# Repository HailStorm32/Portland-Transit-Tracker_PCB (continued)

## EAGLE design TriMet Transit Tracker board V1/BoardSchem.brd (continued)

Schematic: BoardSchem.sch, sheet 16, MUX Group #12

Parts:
IC27, IC28: 74ALVC04PW,118; SOP65P640X110-14N
R60, R61, R62, R63, R64, R65, R66, R67: 50; R0805
U13: 74LCX138MX; SOIC127P600X175-16N
Y1G12, Y2G12, Y3G12, Y4G12, Y5G12, Y6G12, Y7G12, Y8G12: LTST-C170TBKT; LEDC2012X120N

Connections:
+3V3: IC27.14 (VCC), IC28.14 (VCC), U13.16 (VCC); also elsewhere on the board
GND: IC27.7 (GND), IC28.7 (GND), R60.1, R61.1, R62.1, R63.1, R64.1, R65.1, R66.1, R67.1, U13.4 (~E1), U13.5 (~E2), U13.8 (GND); also elsewhere on the board
MUX_GROUP_12: U13.6 (E3); also elsewhere on the board
unnamed: IC27.1 (1A), U13.15 (~O0)
unnamed: IC27.2 (1Y), Y1G12.2 (A)
unnamed: IC27.3 (2A), U13.14 (~O1)
unnamed: IC27.4 (2Y), Y2G12.2 (A)
unnamed: IC27.5 (3A), U13.13 (~O2)
unnamed: IC27.6 (3Y), Y3G12.2 (A)
unnamed: IC27.13 (6A), U13.12 (~O3)
unnamed: IC27.12 (6Y), Y4G12.2 (A)
unnamed: IC27.11 (5A), U13.11 (~O4)
unnamed: IC27.10 (5Y), Y5G12.2 (A)
unnamed: IC27.9 (4A), U13.10 (~O5)
unnamed: IC27.8 (4Y), Y6G12.2 (A)
unnamed: IC28.1 (1A), U13.9 (~O6)
unnamed: IC28.2 (1Y), Y7G12.2 (A)
unnamed: IC28.3 (2A), U13.7 (~O7)
unnamed: IC28.4 (2Y), Y8G12.2 (A)
unnamed: R60.2, Y1G12.1 (K)
unnamed: R61.2, Y2G12.1 (K)
unnamed: R62.2, Y3G12.1 (K)
unnamed: R63.2, Y4G12.1 (K)
unnamed: R64.2, Y5G12.1 (K)
unnamed: R65.2, Y6G12.1 (K)
unnamed: R66.2, Y7G12.1 (K)
unnamed: R67.2, Y8G12.1 (K)
Q0: U13.1 (A0); also elsewhere on the board
Q1: U13.2 (A1); also elsewhere on the board
Q2: U13.3 (A2); also elsewhere on the board

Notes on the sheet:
Blue dont need resistors
MUX Group #12

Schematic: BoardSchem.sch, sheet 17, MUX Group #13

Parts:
B1G13, B2G13, B3G13, B4G13, B5G13, B6G13, B7G13, B8G13: LTST-C170TBKT; LEDC2012X120N
IC29, IC30: 74ALVC04PW,118; SOP65P640X110-14N
U14: 74LCX138MX; SOIC127P600X175-16N

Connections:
+3V3: IC29.14 (VCC), IC30.14 (VCC), U14.16 (VCC); also elsewhere on the board
GND: B1G13.1 (K), B2G13.1 (K), B3G13.1 (K), B4G13.1 (K), B5G13.1 (K), B6G13.1 (K), B7G13.1 (K), B8G13.1 (K), IC29.7 (GND), IC30.7 (GND), U14.4 (~E1), U14.5 (~E2), U14.8 (GND); also elsewhere on the board
MUX_GROUP_13: U14.6 (E3); also elsewhere on the board
unnamed: IC29.1 (1A), U14.15 (~O0)
unnamed: B1G13.2 (A), IC29.2 (1Y)
unnamed: IC29.3 (2A), U14.14 (~O1)
unnamed: B2G13.2 (A), IC29.4 (2Y)
unnamed: IC29.5 (3A), U14.13 (~O2)
unnamed: B3G13.2 (A), IC29.6 (3Y)
unnamed: IC29.13 (6A), U14.12 (~O3)
unnamed: B4G13.2 (A), IC29.12 (6Y)
unnamed: IC29.11 (5A), U14.11 (~O4)
unnamed: B5G13.2 (A), IC29.10 (5Y)
unnamed: IC29.9 (4A), U14.10 (~O5)
unnamed: B6G13.2 (A), IC29.8 (4Y)
unnamed: IC30.1 (1A), U14.9 (~O6)
unnamed: B7G13.2 (A), IC30.2 (1Y)
unnamed: IC30.3 (2A), U14.7 (~O7)
unnamed: B8G13.2 (A), IC30.4 (2Y)
Q0: U14.1 (A0); also elsewhere on the board
Q1: U14.2 (A1); also elsewhere on the board
Q2: U14.3 (A2); also elsewhere on the board

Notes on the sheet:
Blue dont need resistors
MUX Group #13

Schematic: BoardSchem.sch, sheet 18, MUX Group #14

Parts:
G1G14, G2G14, G3G14, G4G14, G5G14, G6G14, G7G14, G8G14: LTST-C170TBKT; LEDC2012X120N
IC31, IC32: 74ALVC04PW,118; SOP65P640X110-14N
R68, R69, R70, R71, R72, R73, R74, R75: 50; R0805
U15: 74LCX138MX; SOIC127P600X175-16N

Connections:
+3V3: IC31.14 (VCC), IC32.14 (VCC), U15.16 (VCC); also elsewhere on the board
GND: IC31.7 (GND), IC32.7 (GND), R68.1, R69.1, R70.1, R71.1, R72.1, R73.1, R74.1, R75.1, U15.4 (~E1), U15.5 (~E2), U15.8 (GND); also elsewhere on the board
MUX_GROUP_14: U15.6 (E3); also elsewhere on the board
unnamed: IC31.1 (1A), U15.15 (~O0)
unnamed: G1G14.2 (A), IC31.2 (1Y)
unnamed: IC31.3 (2A), U15.14 (~O1)
unnamed: G2G14.2 (A), IC31.4 (2Y)
unnamed: IC31.5 (3A), U15.13 (~O2)
unnamed: G3G14.2 (A), IC31.6 (3Y)
unnamed: IC31.13 (6A), U15.12 (~O3)
unnamed: G4G14.2 (A), IC31.12 (6Y)
unnamed: IC31.11 (5A), U15.11 (~O4)
unnamed: G5G14.2 (A), IC31.10 (5Y)
unnamed: IC31.9 (4A), U15.10 (~O5)
unnamed: G6G14.2 (A), IC31.8 (4Y)
unnamed: IC32.1 (1A), U15.9 (~O6)
unnamed: G7G14.2 (A), IC32.2 (1Y)
unnamed: IC32.3 (2A), U15.7 (~O7)
unnamed: G8G14.2 (A), IC32.4 (2Y)
unnamed: G1G14.1 (K), R68.2
unnamed: G2G14.1 (K), R69.2
unnamed: G3G14.1 (K), R70.2
unnamed: G4G14.1 (K), R71.2
unnamed: G5G14.1 (K), R72.2
unnamed: G6G14.1 (K), R73.2
unnamed: G7G14.1 (K), R74.2
unnamed: G8G14.1 (K), R75.2
Q0: U15.1 (A0); also elsewhere on the board
Q1: U15.2 (A1); also elsewhere on the board
Q2: U15.3 (A2); also elsewhere on the board

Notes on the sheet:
Blue dont need resistors
MUX Group #14

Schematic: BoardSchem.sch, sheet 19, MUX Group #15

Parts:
IC33, IC34: 74ALVC04PW,118; SOP65P640X110-14N
R1G15, R2G15, R3G15, R4G15, R5G15, R6G15, R7G15, R8G15: LTST-C170TBKT; LEDC2012X120N
R76, R77, R78, R79, R80, R81, R82, R83: 50; R0805
U16: 74LCX138MX; SOIC127P600X175-16N

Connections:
+3V3: IC33.14 (VCC), IC34.14 (VCC), U16.16 (VCC); also elsewhere on the board
GND: IC33.7 (GND), IC34.7 (GND), R76.1, R77.1, R78.1, R79.1, R80.1, R81.1, R82.1, R83.1, U16.4 (~E1), U16.5 (~E2), U16.8 (GND); also elsewhere on the board
MUX_GROUP_15: U16.6 (E3); also elsewhere on the board
unnamed: IC33.1 (1A), U16.15 (~O0)
unnamed: IC33.2 (1Y), R1G15.2 (A)
unnamed: IC33.3 (2A), U16.14 (~O1)
unnamed: IC33.4 (2Y), R2G15.2 (A)
unnamed: IC33.5 (3A), U16.13 (~O2)
unnamed: IC33.6 (3Y), R3G15.2 (A)
unnamed: IC33.13 (6A), U16.12 (~O3)
unnamed: IC33.12 (6Y), R4G15.2 (A)
unnamed: IC33.11 (5A), U16.11 (~O4)
unnamed: IC33.10 (5Y), R5G15.2 (A)
unnamed: IC33.9 (4A), U16.10 (~O5)
unnamed: IC33.8 (4Y), R6G15.2 (A)
unnamed: IC34.1 (1A), U16.9 (~O6)
unnamed: IC34.2 (1Y), R7G15.2 (A)
unnamed: IC34.3 (2A), U16.7 (~O7)
unnamed: IC34.4 (2Y), R8G15.2 (A)
unnamed: R1G15.1 (K), R76.2
unnamed: R2G15.1 (K), R77.2
unnamed: R3G15.1 (K), R78.2
unnamed: R4G15.1 (K), R79.2
unnamed: R5G15.1 (K), R80.2
unnamed: R6G15.1 (K), R81.2
unnamed: R7G15.1 (K), R82.2
unnamed: R8G15.1 (K), R83.2
Q0: U16.1 (A0); also elsewhere on the board
Q1: U16.2 (A1); also elsewhere on the board
Q2: U16.3 (A2); also elsewhere on the board

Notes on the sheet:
Blue dont need resistors
MUX Group #15

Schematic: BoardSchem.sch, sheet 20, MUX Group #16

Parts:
B1G16, B2G16, B3G16, B4G16, B5G16, B6G16, B7G16, B8G16: LTST-C170TBKT; LEDC2012X120N
IC35, IC36: 74ALVC04PW,118; SOP65P640X110-14N
U17: 74LCX138MX; SOIC127P600X175-16N

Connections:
+3V3: IC35.14 (VCC), IC36.14 (VCC), U17.16 (VCC); also elsewhere on the board
GND: B1G16.1 (K), B2G16.1 (K), B3G16.1 (K), B4G16.1 (K), B5G16.1 (K), B6G16.1 (K), B7G16.1 (K), B8G16.1 (K), IC35.7 (GND), IC36.7 (GND), U17.4 (~E1), U17.5 (~E2), U17.8 (GND); also elsewhere on the board
MUX_GROUP_16: U17.6 (E3); also elsewhere on the board
unnamed: IC35.1 (1A), U17.15 (~O0)
unnamed: B1G16.2 (A), IC35.2 (1Y)
unnamed: IC35.3 (2A), U17.14 (~O1)
unnamed: B2G16.2 (A), IC35.4 (2Y)
unnamed: IC35.5 (3A), U17.13 (~O2)
unnamed: B3G16.2 (A), IC35.6 (3Y)
unnamed: IC35.13 (6A), U17.12 (~O3)
unnamed: B4G16.2 (A), IC35.12 (6Y)
unnamed: IC35.11 (5A), U17.11 (~O4)
unnamed: B5G16.2 (A), IC35.10 (5Y)
unnamed: IC35.9 (4A), U17.10 (~O5)
unnamed: B6G16.2 (A), IC35.8 (4Y)
unnamed: IC36.1 (1A), U17.9 (~O6)
unnamed: B7G16.2 (A), IC36.2 (1Y)
unnamed: IC36.3 (2A), U17.7 (~O7)
unnamed: B8G16.2 (A), IC36.4 (2Y)
Q0: U17.1 (A0); also elsewhere on the board
Q1: U17.2 (A1); also elsewhere on the board
Q2: U17.3 (A2); also elsewhere on the board

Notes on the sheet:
Blue dont need resistors
MUX Group #16

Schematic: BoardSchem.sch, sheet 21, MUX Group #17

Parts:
B3G17, B4G17, B5G17, B6G17, B7G17, B8G17: LTST-C170TBKT; LEDC2012X120N
IC37, IC38: 74ALVC04PW,118; SOP65P640X110-14N
R1G17, R2G17: LTST-C170TBKT; LEDC2012X120N
R84, R85: 50; R0805
U18: 74LCX138MX; SOIC127P600X175-16N

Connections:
+3V3: IC37.14 (VCC), IC38.14 (VCC), U18.16 (VCC); also elsewhere on the board
GND: B3G17.1 (K), B4G17.1 (K), B5G17.1 (K), B6G17.1 (K), B7G17.1 (K), B8G17.1 (K), IC37.7 (GND), IC38.7 (GND), R84.1, R85.1, U18.4 (~E1), U18.5 (~E2), U18.8 (GND); also elsewhere on the board
MUX_GROUP_17: U18.6 (E3); also elsewhere on the board
unnamed: IC37.1 (1A), U18.15 (~O0)
unnamed: IC37.2 (1Y), R1G17.2 (A)
unnamed: IC37.3 (2A), U18.14 (~O1)
unnamed: IC37.4 (2Y), R2G17.2 (A)
unnamed: IC37.5 (3A), U18.13 (~O2)
unnamed: B3G17.2 (A), IC37.6 (3Y)
unnamed: IC37.13 (6A), U18.12 (~O3)
unnamed: B4G17.2 (A), IC37.12 (6Y)
unnamed: IC37.11 (5A), U18.11 (~O4)
unnamed: B5G17.2 (A), IC37.10 (5Y)
unnamed: IC37.9 (4A), U18.10 (~O5)
unnamed: B6G17.2 (A), IC37.8 (4Y)
unnamed: IC38.1 (1A), U18.9 (~O6)
unnamed: B7G17.2 (A), IC38.2 (1Y)
unnamed: IC38.3 (2A), U18.7 (~O7)
unnamed: B8G17.2 (A), IC38.4 (2Y)
unnamed: R1G17.1 (K), R84.2
unnamed: R2G17.1 (K), R85.2
Q0: U18.1 (A0); also elsewhere on the board
Q1: U18.2 (A1); also elsewhere on the board
Q2: U18.3 (A2); also elsewhere on the board

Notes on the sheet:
Blue dont need resistors
MUX Group #17

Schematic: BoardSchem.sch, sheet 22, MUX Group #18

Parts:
G1G18, G2G18, G3G18, G4G18, G5G18, G6G18, G7G18, G8G18: LTST-C170TBKT; LEDC2012X120N
IC39, IC40: 74ALVC04PW,118; SOP65P640X110-14N
R86, R87, R88, R89, R90, R91, R92, R93: 50; R0805
U19: 74LCX138MX; SOIC127P600X175-16N

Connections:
+3V3: IC39.14 (VCC), IC40.14 (VCC), U19.16 (VCC); also elsewhere on the board
GND: IC39.7 (GND), IC40.7 (GND), R86.1, R87.1, R88.1, R89.1, R90.1, R91.1, R92.1, R93.1, U19.4 (~E1), U19.5 (~E2), U19.8 (GND); also elsewhere on the board
MUX_GROUP_18: U19.6 (E3); also elsewhere on the board
unnamed: IC39.1 (1A), U19.15 (~O0)
unnamed: G1G18.2 (A), IC39.2 (1Y)
unnamed: IC39.3 (2A), U19.14 (~O1)
unnamed: G2G18.2 (A), IC39.4 (2Y)
unnamed: IC39.5 (3A), U19.13 (~O2)
unnamed: G3G18.2 (A), IC39.6 (3Y)
unnamed: IC39.13 (6A), U19.12 (~O3)
unnamed: G4G18.2 (A), IC39.12 (6Y)
unnamed: IC39.11 (5A), U19.11 (~O4)
unnamed: G5G18.2 (A), IC39.10 (5Y)
unnamed: IC39.9 (4A), U19.10 (~O5)
unnamed: G6G18.2 (A), IC39.8 (4Y)
unnamed: IC40.1 (1A), U19.9 (~O6)
unnamed: G7G18.2 (A), IC40.2 (1Y)
unnamed: IC40.3 (2A), U19.7 (~O7)
unnamed: G8G18.2 (A), IC40.4 (2Y)
unnamed: G1G18.1 (K), R86.2
unnamed: G2G18.1 (K), R87.2
unnamed: G3G18.1 (K), R88.2
unnamed: G4G18.1 (K), R89.2
unnamed: G5G18.1 (K), R90.2
unnamed: G6G18.1 (K), R91.2
unnamed: G7G18.1 (K), R92.2
unnamed: G8G18.1 (K), R93.2
Q0: U19.1 (A0); also elsewhere on the board
Q1: U19.2 (A1); also elsewhere on the board
Q2: U19.3 (A2); also elsewhere on the board

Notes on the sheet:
Blue dont need resistors
MUX Group #18

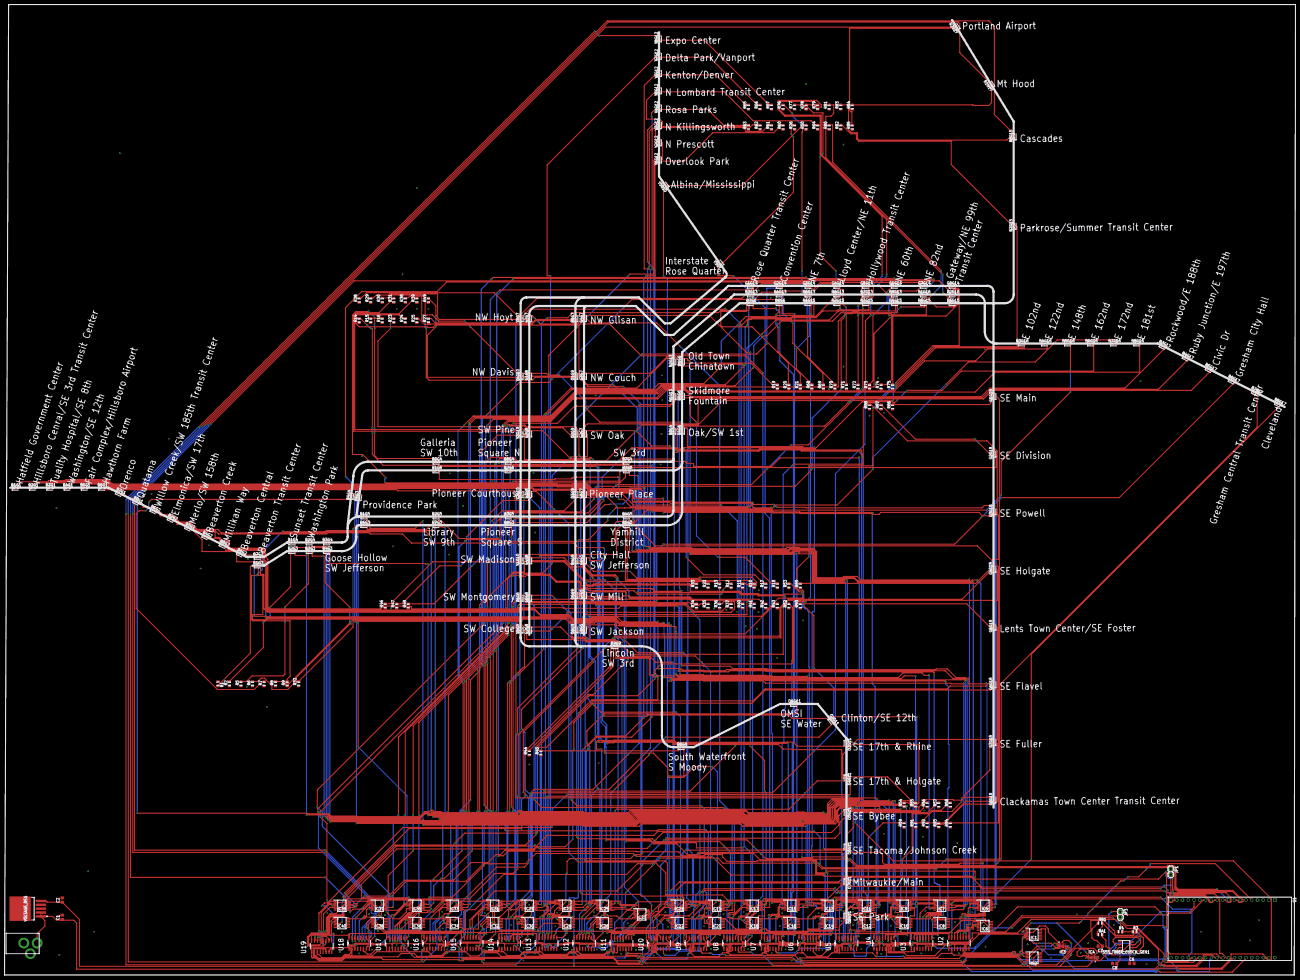
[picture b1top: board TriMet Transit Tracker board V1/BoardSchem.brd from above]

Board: 2 copper layers, 568.6 x 427.5 mm, 303 parts (0 on the bottom side), 412 nets.

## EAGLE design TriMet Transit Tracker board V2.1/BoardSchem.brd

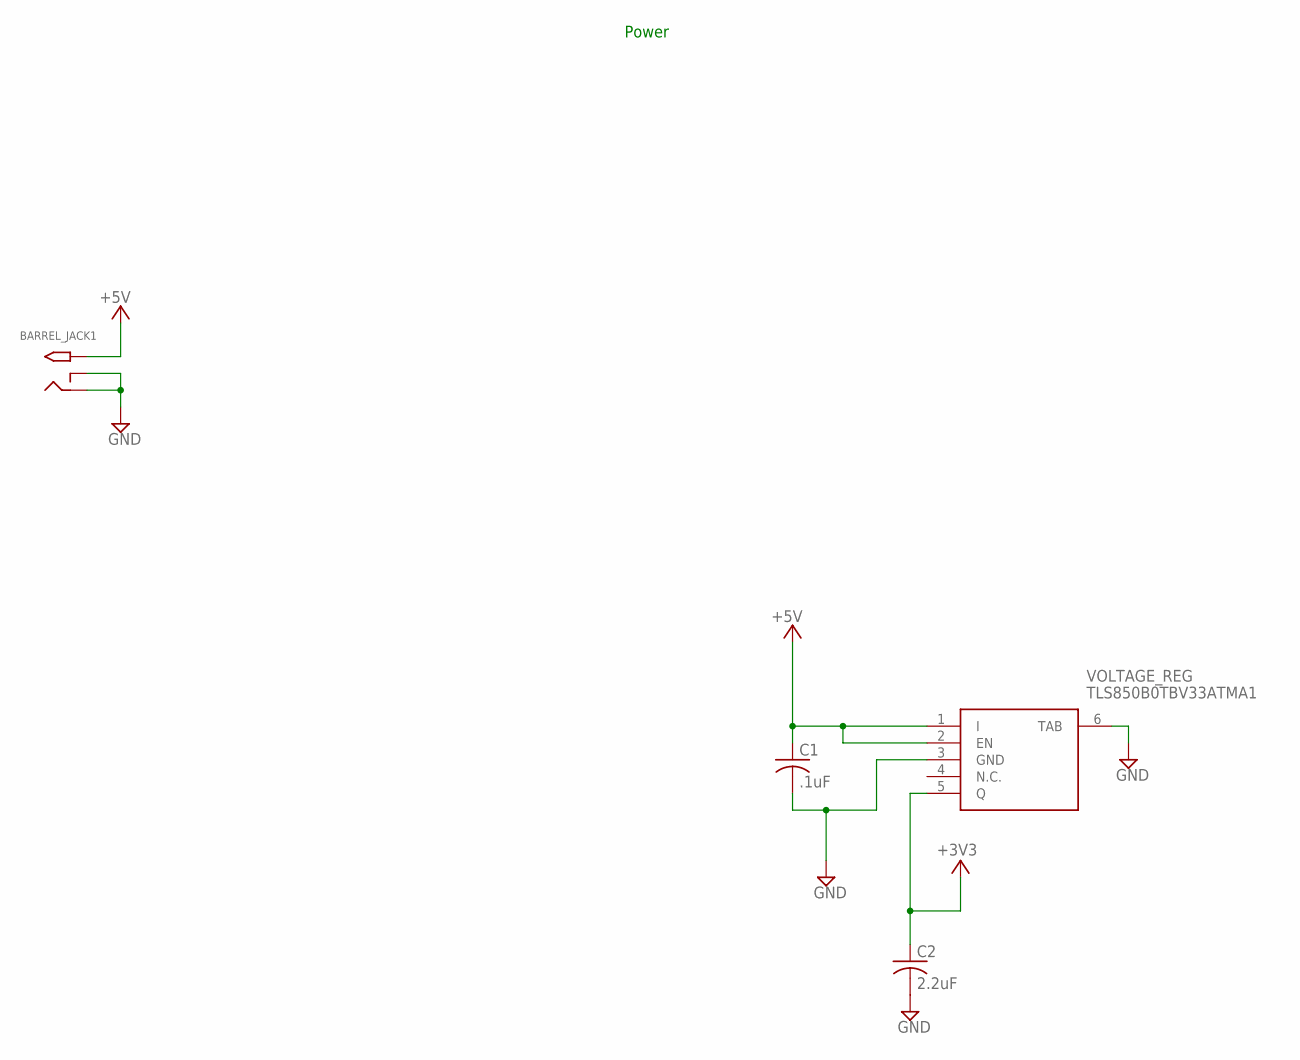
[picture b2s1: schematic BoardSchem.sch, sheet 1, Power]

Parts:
BARREL_JACK1: 2.1MMJACKTHM; PJ-102A
C1: .1uF; C0805
C2: 2.2uF; C0805
VOLTAGE_REG: TLS850B0TBV33ATMA1

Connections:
+3V3: C2.1, VOLTAGE_REG.5 (Q); also elsewhere on the board
+5V: BARREL_JACK1.TIP, C1.1, VOLTAGE_REG.1 (I), VOLTAGE_REG.2 (EN); also elsewhere on the board
GND: BARREL_JACK1.RING, BARREL_JACK1.RING_SW, C1.2, C2.2, VOLTAGE_REG.3 (GND), VOLTAGE_REG.6 (TAB); also elsewhere on the board

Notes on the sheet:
Power

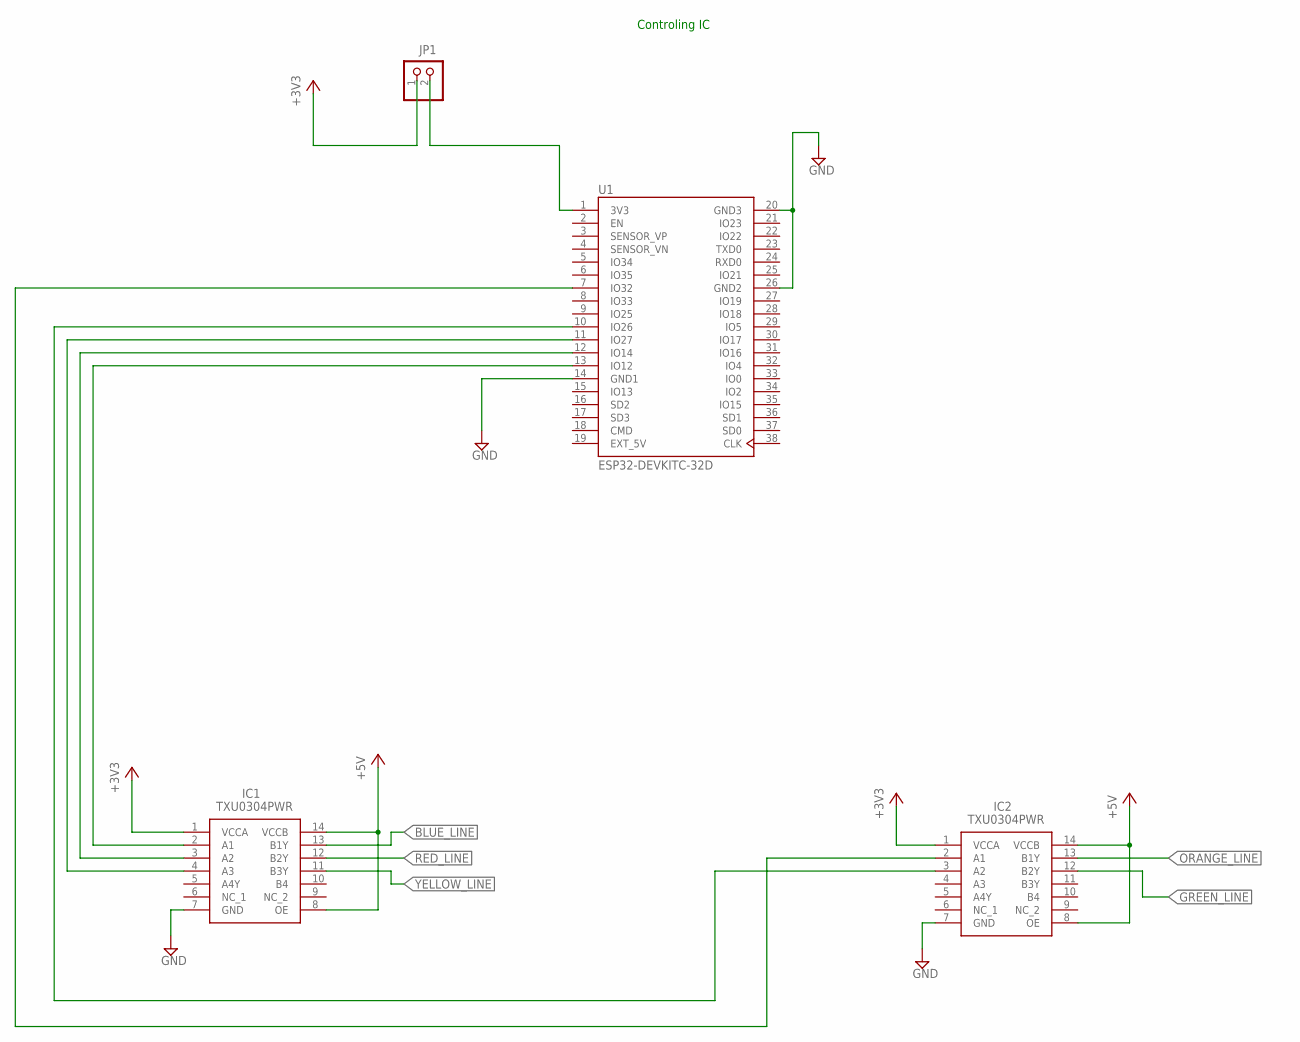
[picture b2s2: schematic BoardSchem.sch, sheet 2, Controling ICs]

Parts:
IC1, IC2: TXU0304PWR; SOP65P640X120-14N
JP1: PINHD-1X2; 1X02
U1: ESP32-DEVKITC-32D; MODULE_ESP32-DEVKITC-32D

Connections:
+3V3: IC1.1 (VCCA), IC2.1 (VCCA), JP1.1; also elsewhere on the board
+5V: IC1.8 (OE), IC1.14 (VCCB), IC2.8 (OE), IC2.14 (VCCB); also elsewhere on the board
BLUE_LINE: IC1.13 (B1Y); also elsewhere on the board
EXT_5V: U1.19 (EXT_5V)
GND: IC1.7 (GND), IC2.7 (GND), U1.14 (GND1), U1.20 (GND3), U1.26 (GND2); also elsewhere on the board
GREEN_LINE: IC2.12 (B2Y); also elsewhere on the board
unnamed: JP1.2, U1.1 (3V3)
unnamed: IC1.2 (A1), U1.13 (IO12)
unnamed: IC1.3 (A2), U1.12 (IO14)
unnamed: IC1.4 (A3), U1.11 (IO27)
unnamed: IC2.3 (A2), U1.10 (IO26)
unnamed: IC2.2 (A1), U1.7 (IO32)
ORANGE_LINE: IC2.13 (B1Y); also elsewhere on the board
RED_LINE: IC1.12 (B2Y); also elsewhere on the board
YELLOW_LINE: IC1.11 (B3Y); also elsewhere on the board

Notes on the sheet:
Controling IC

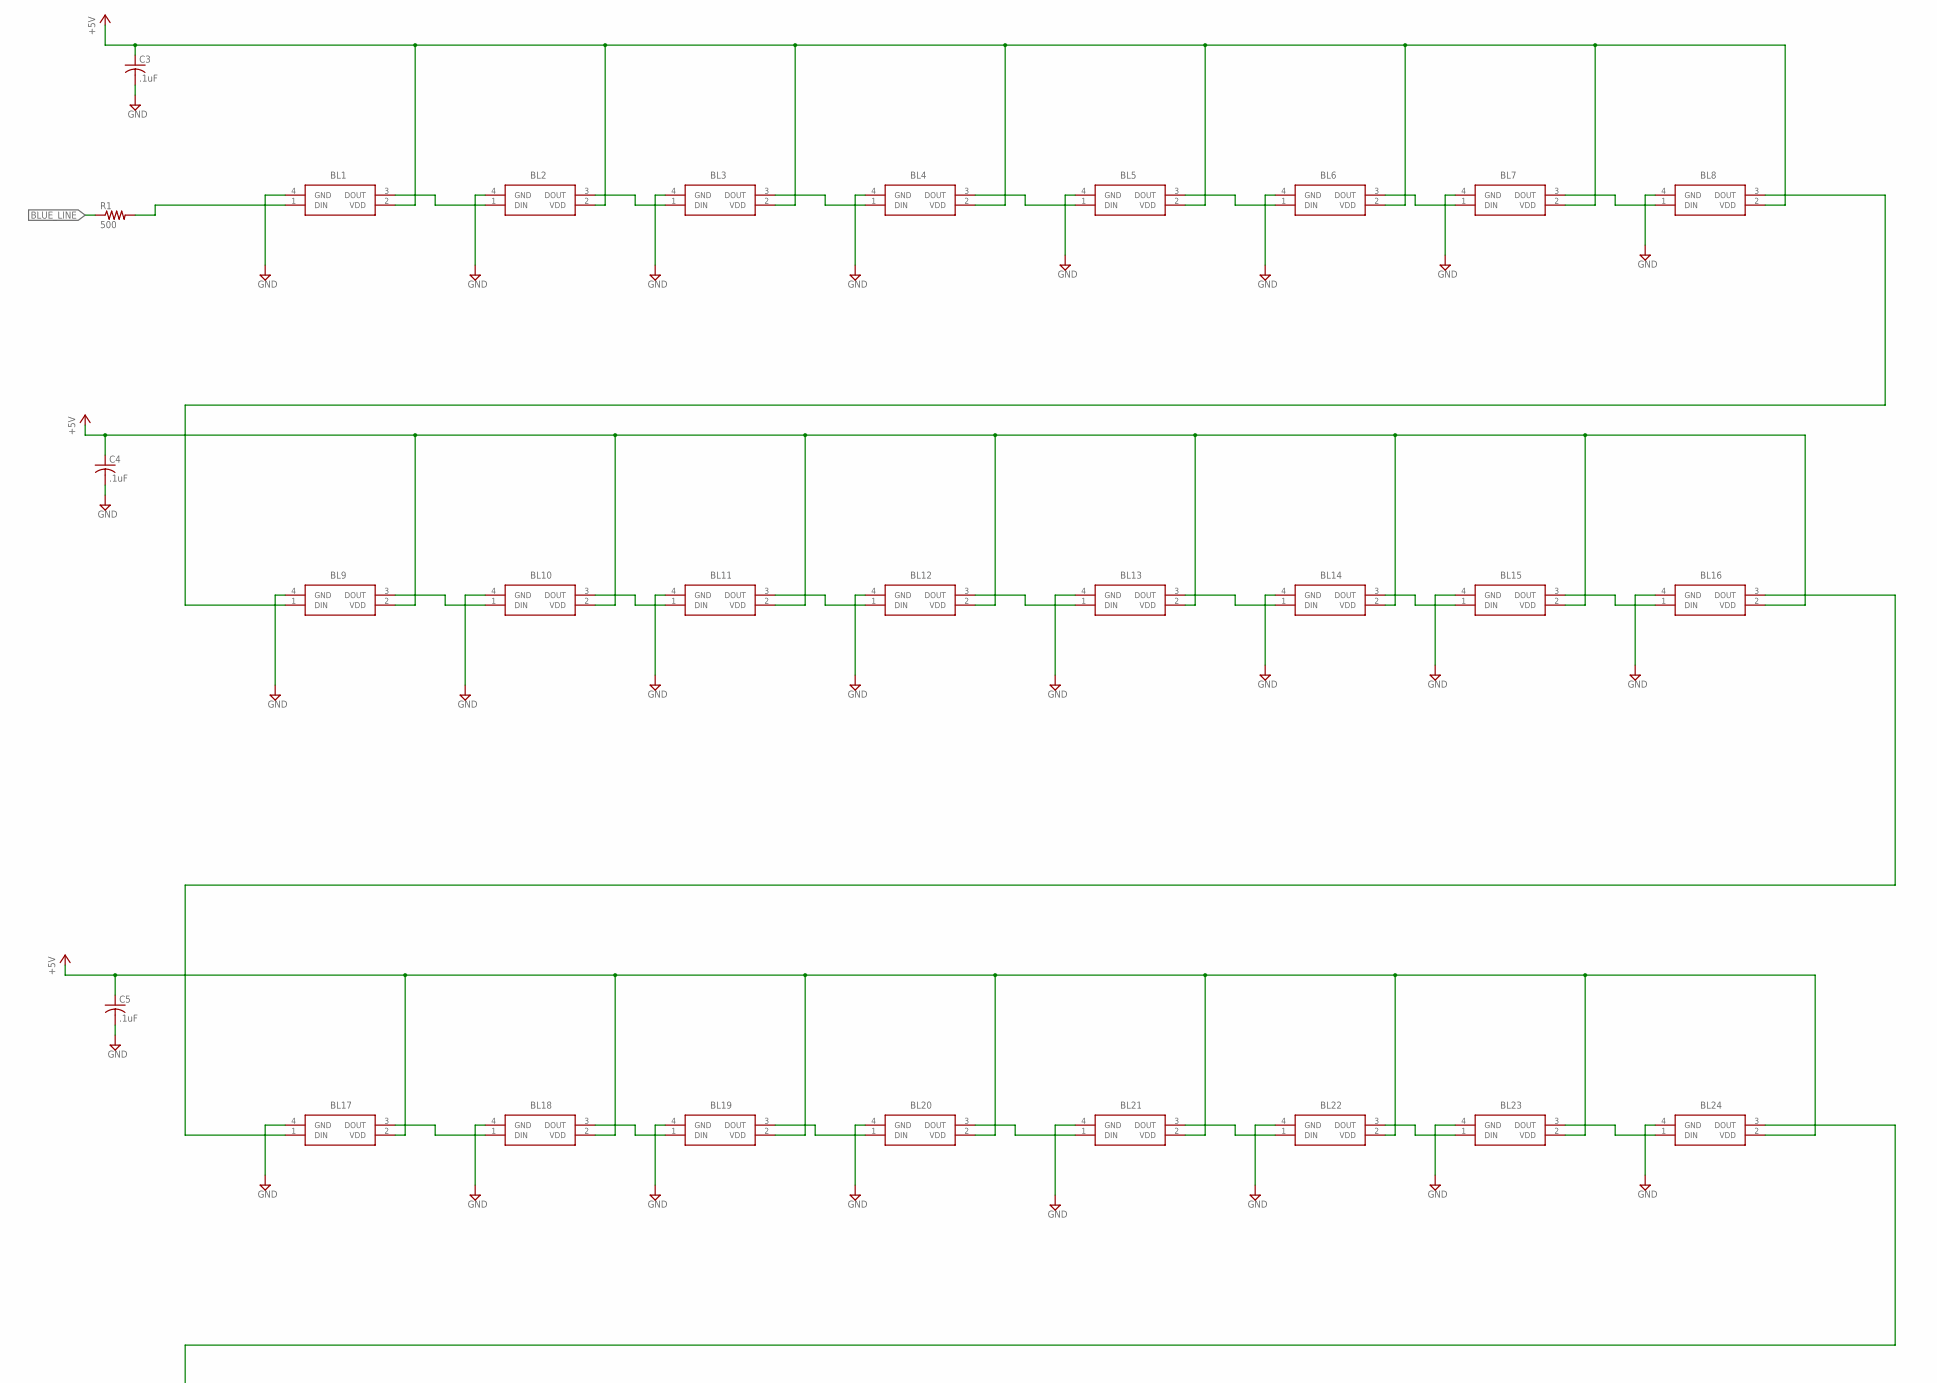
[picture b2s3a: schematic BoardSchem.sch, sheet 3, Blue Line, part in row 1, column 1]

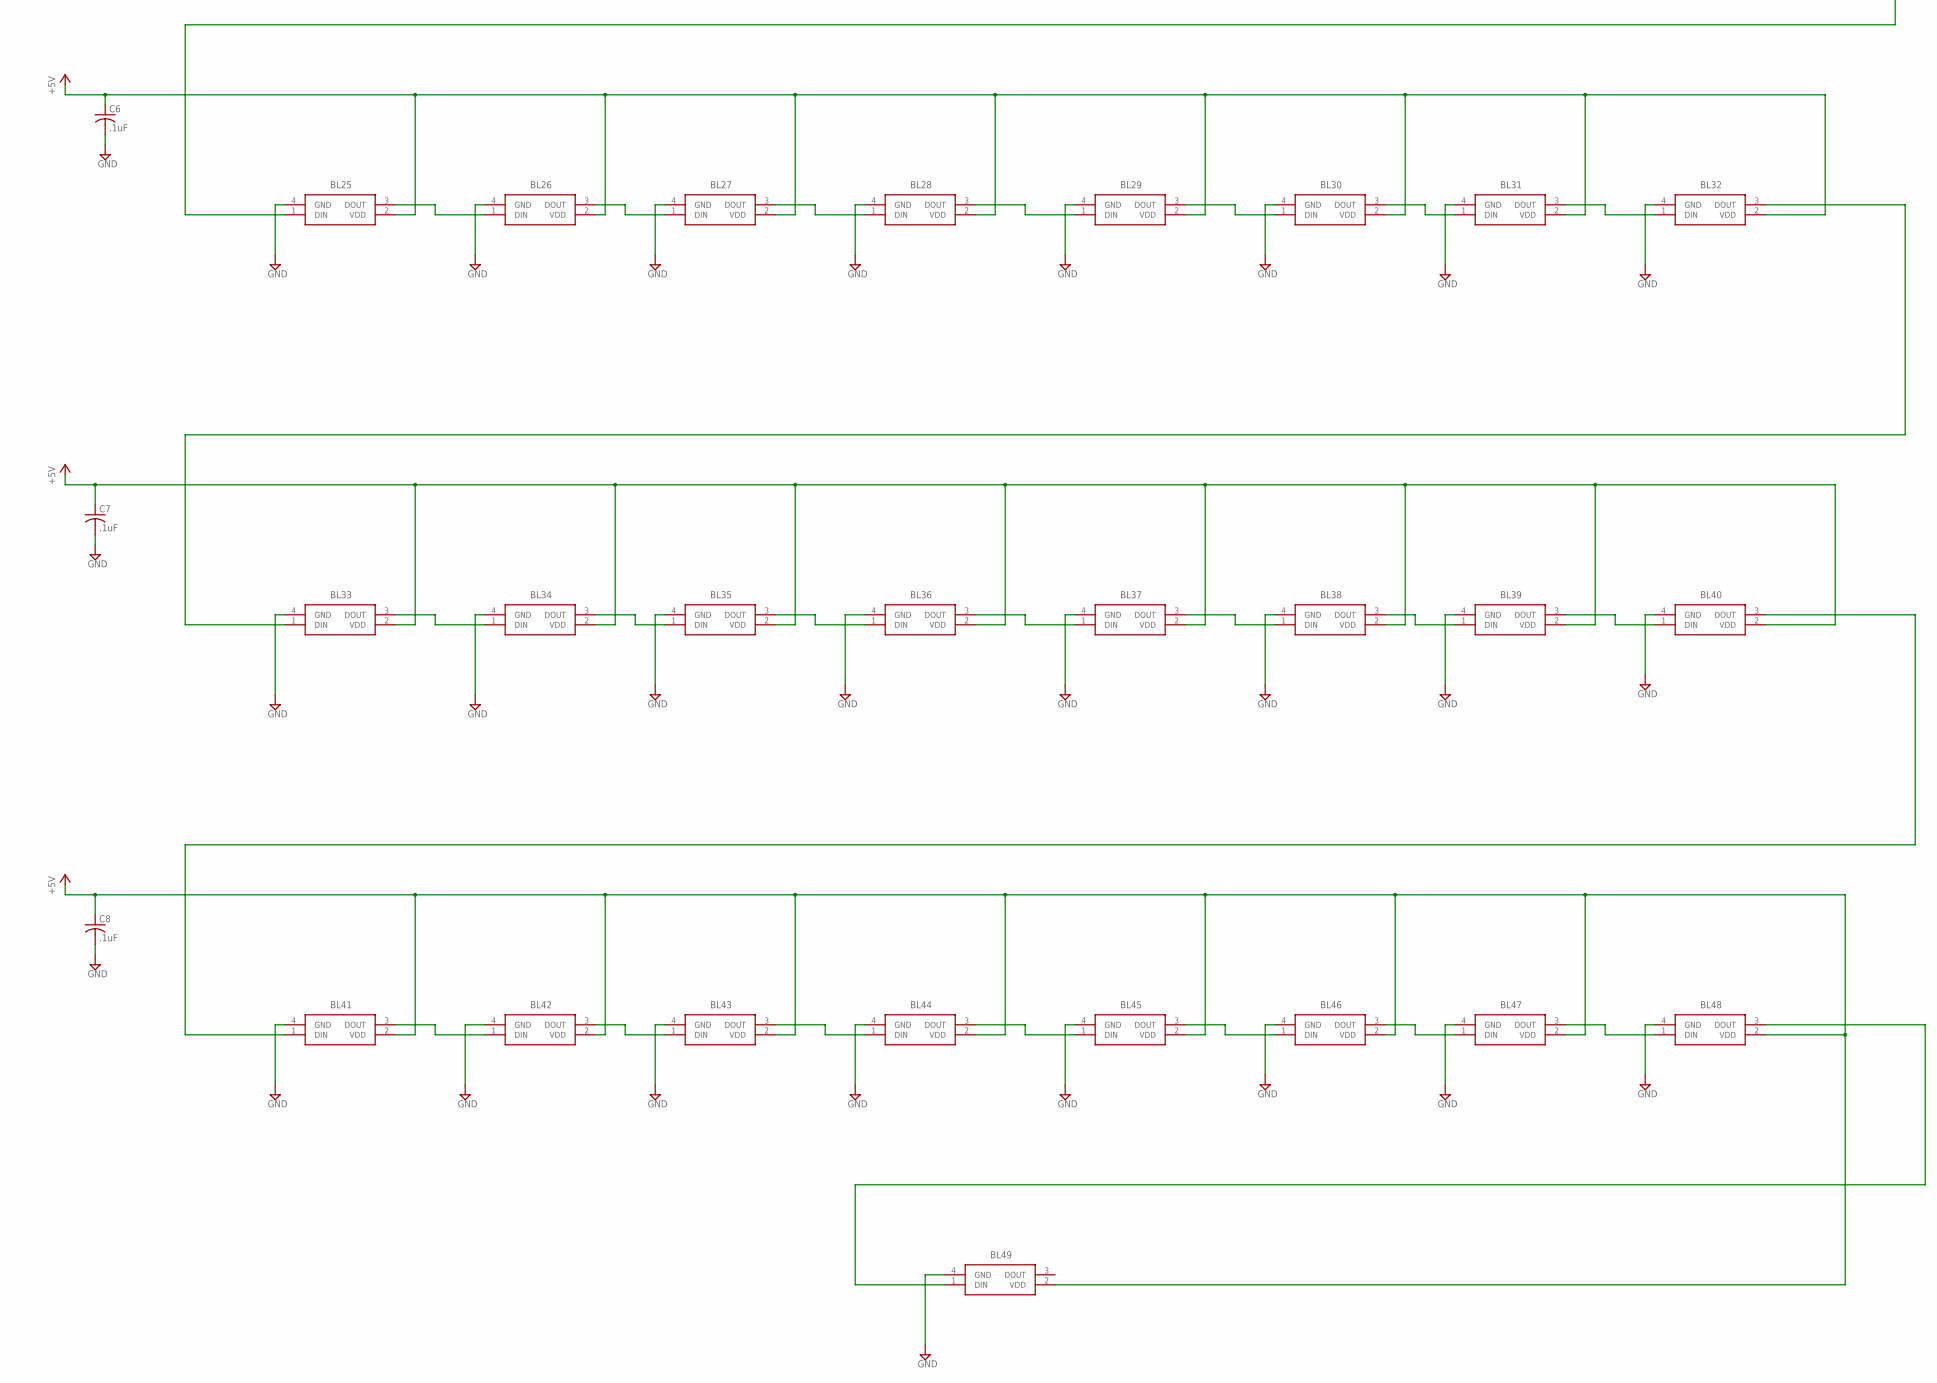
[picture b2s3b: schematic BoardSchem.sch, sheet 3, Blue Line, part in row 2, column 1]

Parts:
BL1, BL2, BL3, BL4, BL5, BL6, BL7, BL8, BL9, BL10, BL11, BL12, BL13, BL14, BL15, BL16, BL17, BL18, BL19, BL20, BL21, BL22, BL23, BL24, BL25, BL26, BL27, BL28, BL29, BL30, BL31, BL32, BL33, BL34, BL35, BL36, BL37, BL38, BL39, BL40, BL41, BL42, BL43, BL44, BL45, BL46, BL47, BL48, BL49: 4492__SK6805-EC_15_; 4492SK6805EC15
C3, C4, C5, C6, C7, C8: .1uF; C0805
R1: 500; R0805

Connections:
+5V: BL1.2 (VDD), BL2.2 (VDD), BL3.2 (VDD), BL4.2 (VDD), BL5.2 (VDD), BL6.2 (VDD), BL7.2 (VDD), BL8.2 (VDD), BL9.2 (VDD), BL10.2 (VDD), BL11.2 (VDD), BL12.2 (VDD), BL13.2 (VDD), BL14.2 (VDD), BL15.2 (VDD), BL16.2 (VDD), BL17.2 (VDD), BL18.2 (VDD), BL19.2 (VDD), BL20.2 (VDD), BL21.2 (VDD), BL22.2 (VDD), BL23.2 (VDD), BL24.2 (VDD), BL25.2 (VDD), BL26.2 (VDD), BL27.2 (VDD), BL28.2 (VDD), BL29.2 (VDD), BL30.2 (VDD), BL31.2 (VDD), BL32.2 (VDD), BL33.2 (VDD), BL34.2 (VDD), BL35.2 (VDD), BL36.2 (VDD), BL37.2 (VDD), BL38.2 (VDD), BL39.2 (VDD), BL40.2 (VDD), BL41.2 (VDD), BL42.2 (VDD), BL43.2 (VDD), BL44.2 (VDD), BL45.2 (VDD), BL46.2 (VDD), BL47.2 (VDD), BL48.2 (VDD), BL49.2 (VDD), C3.1, C4.1, C5.1, C6.1, C7.1, C8.1; also elsewhere on the board
BLUE_LINE: R1.1; also elsewhere on the board
GND: BL1.4 (GND), BL2.4 (GND), BL3.4 (GND), BL4.4 (GND), BL5.4 (GND), BL6.4 (GND), BL7.4 (GND), BL8.4 (GND), BL9.4 (GND), BL10.4 (GND), BL11.4 (GND), BL12.4 (GND), BL13.4 (GND), BL14.4 (GND), BL15.4 (GND), BL16.4 (GND), BL17.4 (GND), BL18.4 (GND), BL19.4 (GND), BL20.4 (GND), BL21.4 (GND), BL22.4 (GND), BL23.4 (GND), BL24.4 (GND), BL25.4 (GND), BL26.4 (GND), BL27.4 (GND), BL28.4 (GND), BL29.4 (GND), BL30.4 (GND), BL31.4 (GND), BL32.4 (GND), BL33.4 (GND), BL34.4 (GND), BL35.4 (GND), BL36.4 (GND), BL37.4 (GND), BL38.4 (GND), BL39.4 (GND), BL40.4 (GND), BL41.4 (GND), BL42.4 (GND), BL43.4 (GND), BL44.4 (GND), BL45.4 (GND), BL46.4 (GND), BL47.4 (GND), BL48.4 (GND), BL49.4 (GND), C3.2, C4.2, C5.2, C6.2, C7.2, C8.2; also elsewhere on the board
unnamed: BL1.3 (DOUT), BL2.1 (DIN)
unnamed: BL2.3 (DOUT), BL3.1 (DIN)
unnamed: BL3.3 (DOUT), BL4.1 (DIN)
unnamed: BL4.3 (DOUT), BL5.1 (DIN)
unnamed: BL5.3 (DOUT), BL6.1 (DIN)
unnamed: BL6.3 (DOUT), BL7.1 (DIN)
unnamed: BL7.3 (DOUT), BL8.1 (DIN)
unnamed: BL8.3 (DOUT), BL9.1 (DIN)
unnamed: BL9.3 (DOUT), BL10.1 (DIN)
unnamed: BL10.3 (DOUT), BL11.1 (DIN)
unnamed: BL11.3 (DOUT), BL12.1 (DIN)
unnamed: BL12.3 (DOUT), BL13.1 (DIN)
unnamed: BL13.3 (DOUT), BL14.1 (DIN)
unnamed: BL14.3 (DOUT), BL15.1 (DIN)
unnamed: BL15.3 (DOUT), BL16.1 (DIN)
unnamed: BL16.3 (DOUT), BL17.1 (DIN)
unnamed: BL17.3 (DOUT), BL18.1 (DIN)
unnamed: BL18.3 (DOUT), BL19.1 (DIN)
unnamed: BL19.3 (DOUT), BL20.1 (DIN)
unnamed: BL20.3 (DOUT), BL21.1 (DIN)
unnamed: BL21.3 (DOUT), BL22.1 (DIN)
unnamed: BL22.3 (DOUT), BL23.1 (DIN)
unnamed: BL23.3 (DOUT), BL24.1 (DIN)
unnamed: BL24.3 (DOUT), BL25.1 (DIN)
unnamed: BL25.3 (DOUT), BL26.1 (DIN)
unnamed: BL26.3 (DOUT), BL27.1 (DIN)
unnamed: BL27.3 (DOUT), BL28.1 (DIN)
unnamed: BL28.3 (DOUT), BL29.1 (DIN)
unnamed: BL29.3 (DOUT), BL30.1 (DIN)
unnamed: BL30.3 (DOUT), BL31.1 (DIN)
unnamed: BL31.3 (DOUT), BL32.1 (DIN)
unnamed: BL32.3 (DOUT), BL33.1 (DIN)
unnamed: BL33.3 (DOUT), BL34.1 (DIN)
unnamed: BL34.3 (DOUT), BL35.1 (DIN)
unnamed: BL35.3 (DOUT), BL36.1 (DIN)
unnamed: BL36.3 (DOUT), BL37.1 (DIN)
unnamed: BL37.3 (DOUT), BL38.1 (DIN)
unnamed: BL38.3 (DOUT), BL39.1 (DIN)
unnamed: BL39.3 (DOUT), BL40.1 (DIN)
unnamed: BL40.3 (DOUT), BL41.1 (DIN)
unnamed: BL41.3 (DOUT), BL42.1 (DIN)
unnamed: BL42.3 (DOUT), BL43.1 (DIN)
unnamed: BL43.3 (DOUT), BL44.1 (DIN)
unnamed: BL44.3 (DOUT), BL45.1 (DIN)
unnamed: BL45.3 (DOUT), BL46.1 (DIN)
unnamed: BL46.3 (DOUT), BL47.1 (DIN)
unnamed: BL47.3 (DOUT), BL48.1 (DIN)
unnamed: BL48.3 (DOUT), BL49.1 (DIN)
unnamed: BL1.1 (DIN), R1.2
